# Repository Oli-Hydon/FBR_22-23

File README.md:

# FBR_22-23
#All files partaining to different parts of the project are contained in branches of this repository
#Hence no files are stored in the main branch

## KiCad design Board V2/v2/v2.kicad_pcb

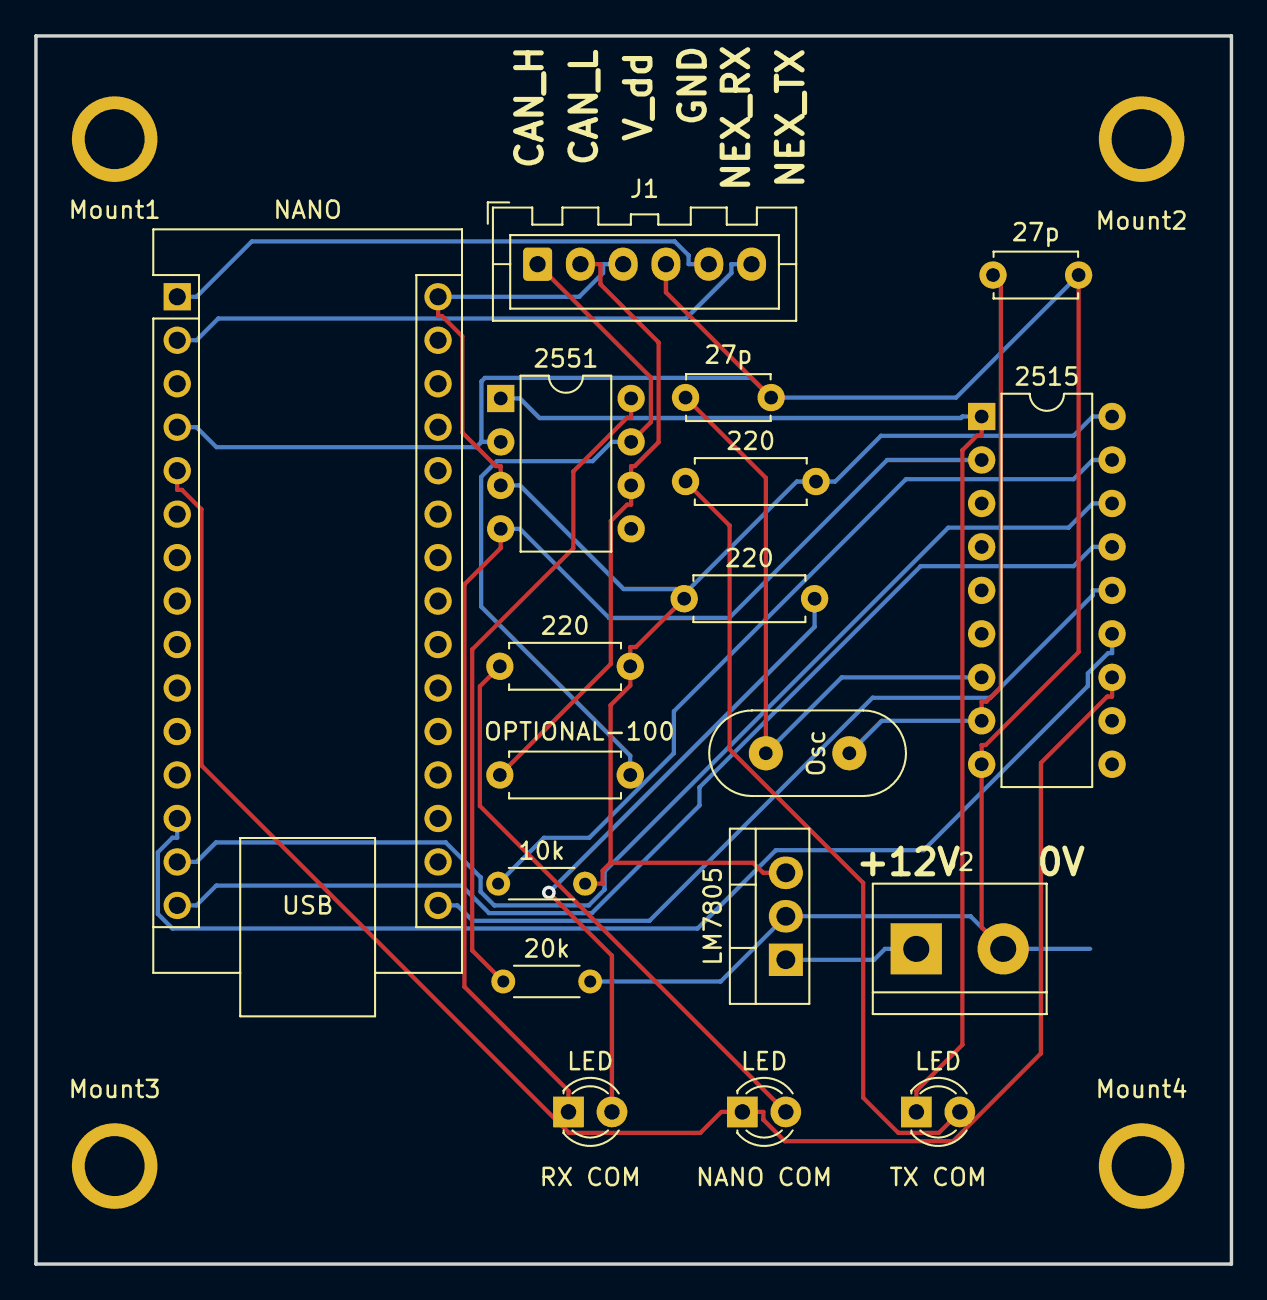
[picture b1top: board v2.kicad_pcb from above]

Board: 2 copper layers, 69.8 x 71.8 mm, 22 parts (0 on the bottom side), 21 nets.

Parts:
10k: 10k; R_Axial_DIN0204_L3.6mm_D1.6mm_P5.08mm_Horizontal
20k: 20k; R_Axial_DIN0204_L3.6mm_D1.6mm_P5.08mm_Horizontal
27p, 27p#2: 27pF; C_Disc_D4.7mm_W2.5mm_P5.00mm
220, 220#2, 220#3: 220; R_Axial_DIN0207_L6.3mm_D2.5mm_P7.62mm_Horizontal
2515: MCP2515-xSO; DIP-18_W7.62mm
2551: MCP2551-I-P; DIP-8_W7.62mm
J1: Conn_01x06_Male; JST_XA_B06B-XASK-1_1x06_P2.50mm_Vertical
J2: Screw_Terminal_01x02; TerminalBlock_bornier-2_P5.08mm
LED: RX COM; LED_D3.0mm
LED#2: TX COM; LED_D3.0mm
LED#3: NANO COM; LED_D3.0mm
LM7805: LM7805_TO220; TO-220-3_Vertical
Mount1, Mount2, Mount3, Mount4: MountingHole_3.5mm_Pad
NANO: Arduino_Nano_v2.x; Arduino_Nano
OPTIONAL-100: 100; R_Axial_DIN0207_L6.3mm_D2.5mm_P7.62mm_Horizontal
Osc: Crystal; 9B-16.000MAAJ-B

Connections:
CANH: 2551.7 (CANH), J1.1, OPTIONAL-100.2
CANL: 2551.6 (CANL), J1.2, OPTIONAL-100.1
CAN_RX: 2515.2 (RXCAN), 2551.4 (RXD), LED.1 (K)
CAN_TX: 2515.1 (TXCAN), 2551.1 (TXD), LED#2.1 (K)
GND: 20k.2, 27p.2, 27p#2.2, 2515.9 (VSS), 2551.2 (VSS), J1.4, J2.2, LM7805.2 (GND), NANO.4 (GND)
NANO 2: 2515.12 (~INT), LED#3.1 (K), NANO.5 (D2)
NEX_RX: J1.5, NANO.1 (D1/TX)
NEX_TX: J1.6, NANO.2 (D0/RX)
unnamed: 2515.13 (SCK), NANO.13 (D10)
unnamed: 2515.16 (~CS), NANO.14 (D11)
unnamed: 2515.15 (SO), NANO.15 (D12)
unnamed: 2515.14 (SI), NANO.16 (D13)
unnamed: 27p#2.1, 2515.7 (OSC2), Osc.1
unnamed: 27p.1, 2515.8 (OSC1), Osc.2
unnamed: 220.2, LED.2 (A)
unnamed: 220#2.1, LED#2.2 (A)
unnamed: 220#3.1, LED#3.2 (A)
unnamed: 20k.1, 2551.8 (Rs)
unnamed: 10k.1, 2515.17 (~RESET)
V_IN: J2.1, LM7805.1 (VI)
V_dd: 10k.2, 220.1, 220#2.2, 220#3.2, 2515.18 (VDD), 2551.3 (VDD), J1.3, LM7805.3 (VO), NANO.30 (VIN)

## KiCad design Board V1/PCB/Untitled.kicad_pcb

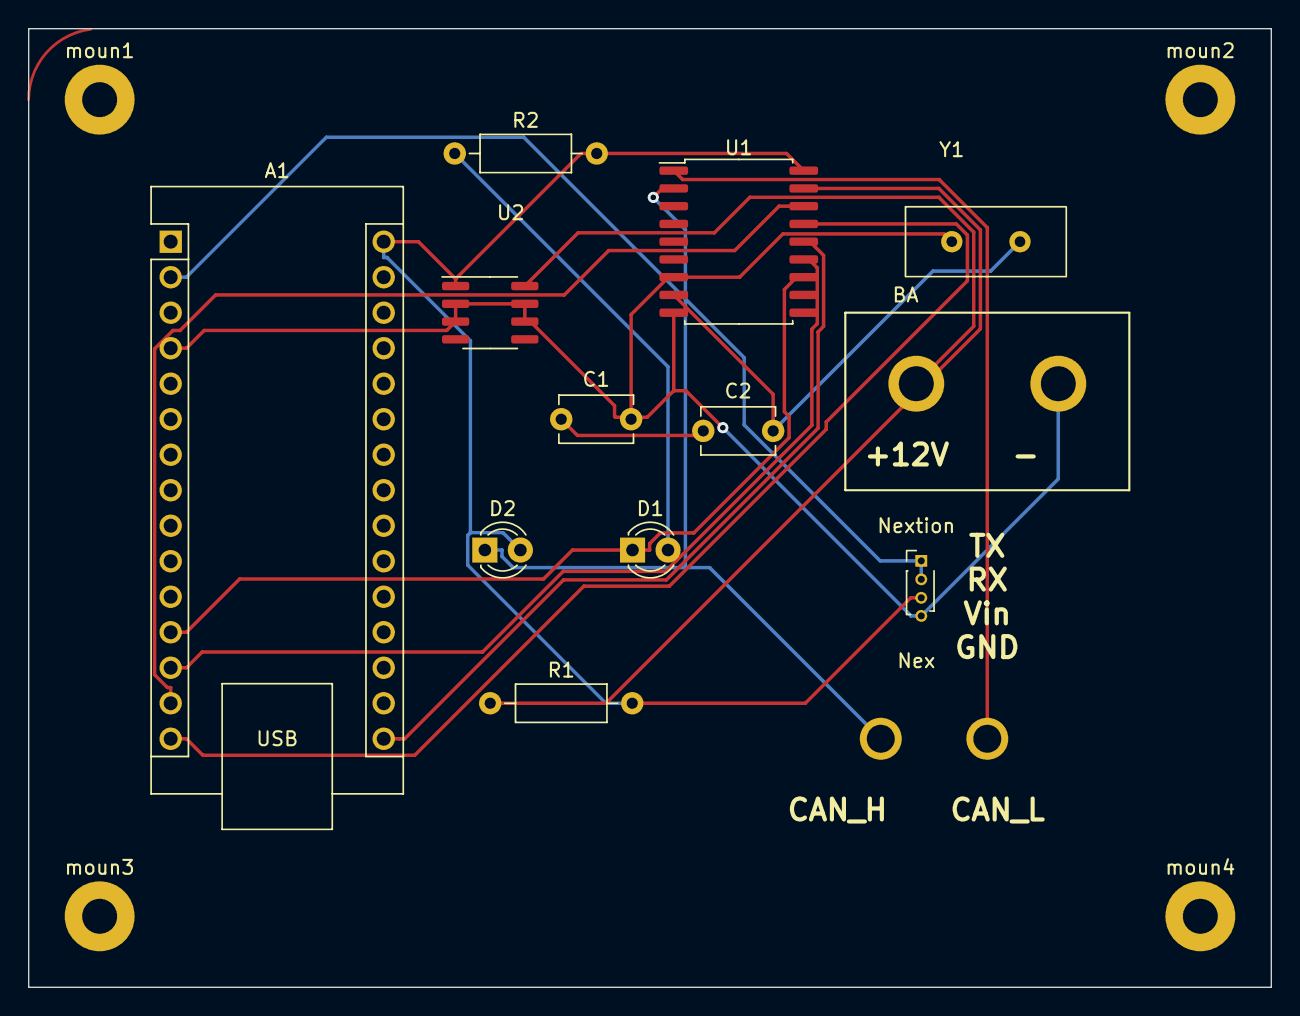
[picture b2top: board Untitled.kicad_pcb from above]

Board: 2 copper layers, 88.9 x 68.6 mm, 17 parts (0 on the bottom side), 16 nets.

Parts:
A1: Arduino_Nano_v3.x; Arduino_Nano
BA: Power Connctor
C1, C2: CAP; C_Disc_D5.1mm_W3.2mm_P5.00mm
D1: INT Activity; LED_D3.0mm
D2: CAN Activity; LED_D3.0mm
Nex: Can Connector Maybe
Nextion: PinHeader_1x04_P200mm_Vertical; PinHeader_1x04_P1.00mm_Vertical
R1: 10k; R_Axial_DIN0207_L6.3mm_D2.5mm_P10.16mm_Horizontal
R2: 220; R_Axial_DIN0207_L6.3mm_D2.5mm_P10.16mm_Horizontal
U1: MCP2515-xSO; SOIC-18W_7.5x11.6mm_P1.27mm
U2: LM78L05_SO8; SOIC-8_3.9x4.9mm_P1.27mm
Y1: 16MHz; 9B-16M
moun1, moun2, moun3, moun4: MountingHole_2.5mm_Pad

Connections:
Can High: D2.1 (K), Nex.1, U1.2 (RXCAN)
Can Low: Nex.2, U1.1 (TXCAN)
Earth: C1.1, C2.1
unnamed: A1.12 (D9), D1.1 (K), U1.12 (~INT)
unnamed: A1.13 (D10), U1.13 (SCK)
unnamed: A1.14 (D11), U1.16 (~CS)
unnamed: A1.15 (D12), U1.15 (SO)
unnamed: A1.16 (D13), U1.14 (SI)
unnamed: C1.2, U1.7 (OSC2), Y1.1
unnamed: C2.2, U1.8 (OSC1), Y1.2
unnamed: D1.2 (A), R2.1
unnamed: R1.1, U1.17 (~RESET)
Nex RX: A1.2 (D0/RX), Nextion.2
Vdd: A1.30 (VIN), D2.2 (A), Nextion.3, R1.2, R2.2, U1.18 (VDD), U2.1 (OUT)
Vin: BA.1, U2.8 (IN)
Vss: A1.4 (GND), BA.2, Nextion.4, U1.9 (VSS), U2.2 (GND), U2.3 (GND), U2.6 (GND), U2.7 (GND)

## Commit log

2023-01-28 idk what changed
2023-01-28 thing
2023-01-28 Delete
2023-01-28 Inital Commit
2023-01-29 Changed graphs and data pages.
2023-01-29 Added ReadMe
2023-01-29 Minor changes
2023-01-29 Added resize option to image creator and used it to replace speedometer images.
2023-01-29 Added object names to nextion file
2023-01-29 Updated object name for nextion display file
2023-01-29 added object names
2023-01-29 Added some function for display home page
2023-01-29 Completed home page update functions
2023-01-29 Added update home page to main
2023-01-29 Small Fixes
2023-02-06 Added new version of board with correct can chips
2023-02-06 added more functino that interact with display
2023-02-06 added various required images
2023-02-12 Added some parts
2023-02-12 Added the correct chips to the board
2023-02-15 Updated the board with Rikesh's changes
2023-03-05 added can recive code
2023-03-11 Added can recive code correctly with pointers
2023-03-12 Finished the bulk of the code except for some small detials
